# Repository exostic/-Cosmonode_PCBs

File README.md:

# Cosmonode v0.7

Universal node, plug and play extensions to ease sensors connection.

## Features

	- Compile and flash with Arduino IDE
	- MCU = ATMega328P-AU
	- radio = RN2483 / RFM69CW ( communications based on LoRaWan or MySensors protocol )
	- 3.3V regulation ( XC6206P332MR )
	- Powered by 3.7V LiPo battery ( 2 pins JST connector )
	- Battery charging ( MCP7831 )
	- State LED's
	- Jumpers to activate radio reset, LED's, on/off switch
	- Button for reset / config mode, or anything else!
	- ATSHA204 to allow hardware unique signature ( no use with RN2483 )

## Projects

Each directory contains Kicad plans, 3D plans, gerber, descriptive .png and .pdf files.

	- ext01 : BME280, Temperature + Humidity + Pression sensor ( only here for the footprint )
	- ext02 : XKC-Y25, Liquid level sensor
	- ext03 : Various connectors ( I2C, Digital, Analog )
	- ext04 : PT100 3 wire, Temperature sensor
	- ext05 : ISP header + micro USB to TTL 
	- ext06 : Analog pH Sensor - BNC probe (WIP)
	- ext07 : MHZ19, CO2 sensor

## Board pinout

	A0 = /
	A1 = /
	A2 = ATSHA204 Input
	A3 = Battery voltage report
	A4 = SDA
	A5 = SCL
	A6 = * LED, jumper J9 ( used as RN2483 Tx )
	A7 = * LED, jumper J14 ( used as RN2483 Rx )
	D0 = RX
	D1 = TX
	D2 = * WakeInterrupt from RN2483, jumper J6 - RFM69 DI0
	D3 = ButtonInterrupt, jumper JP2 ( used to chose mode )
	D4 = /
	D5 = /
	D6 = /
	D7 = /
	D8 = /
	D9 = * RN2483 Reset, jumper J3 - RFM69 Reset
	D10 = RN2483 Rx - RFM69 NSS
	D11 = RN2483 Tx - RFM69 MOSI
	D12 = RFM69 MISO
	D13 = RFM69 SCK
	*optionnal, solder jumper

## Roadmap

--> changelog.md

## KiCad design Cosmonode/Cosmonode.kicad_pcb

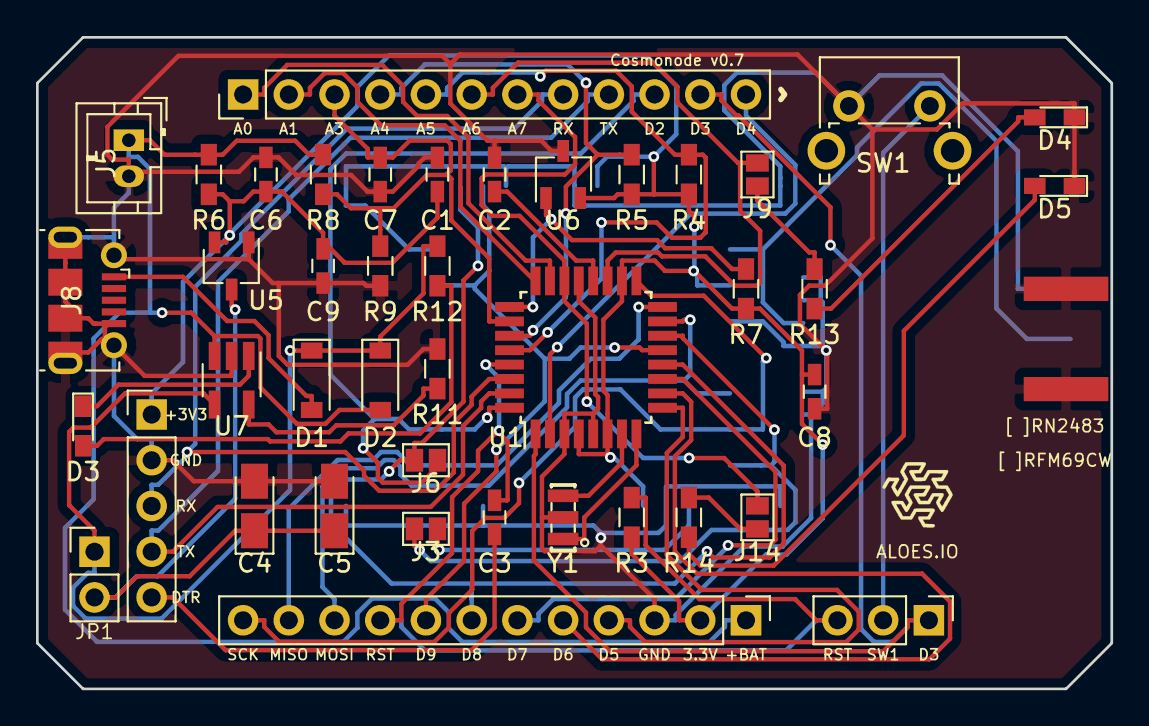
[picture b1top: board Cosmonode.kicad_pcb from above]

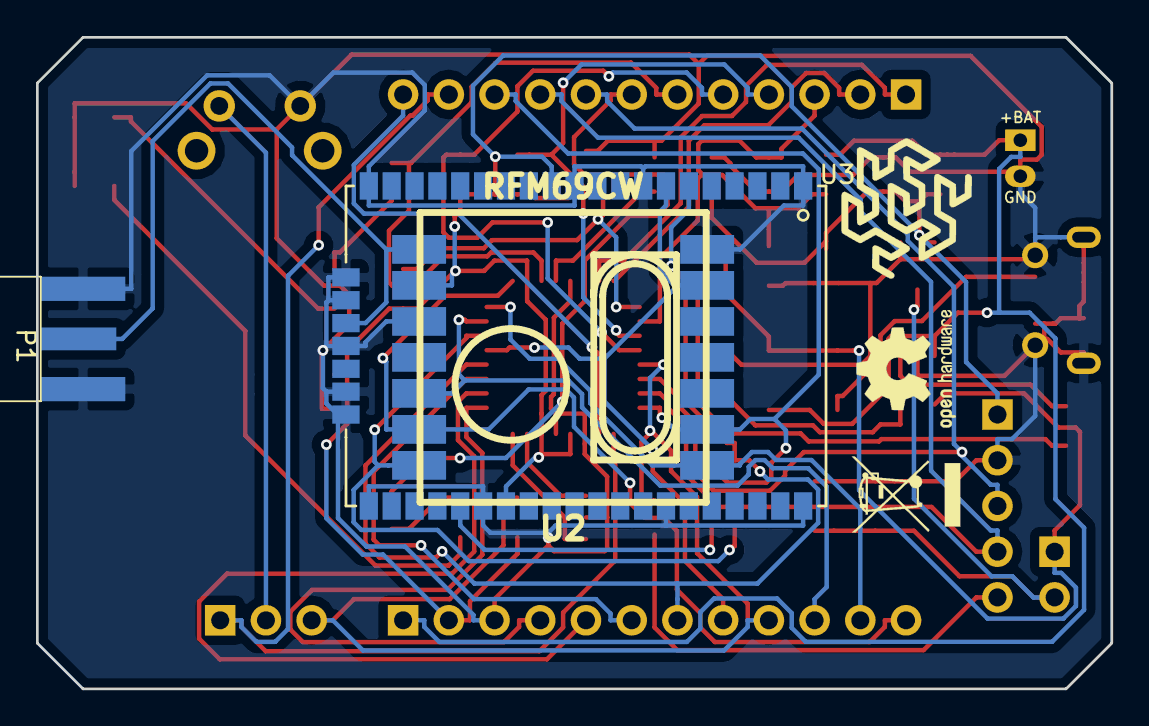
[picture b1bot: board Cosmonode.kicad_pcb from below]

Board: 2 copper layers, 59.7 x 36.2 mm, 49 parts (6 on the bottom side), 43 nets.

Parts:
C1, C2, C3, C7, C8, C9: 100nF; C_0603_HandSoldering
C4, C5: 47uF; CP_Tantalum_Case-A_EIA-3216-18_Reflow
C6: 4.7uF; C_0603_HandSoldering
D1, D2: MBR0520; D_SOD-123
D3, D4, D5: LED; LED_0603_HandSoldering
J1, J2: CONN_01X12; Pin_Header_Straight_1x12_Pitch2.54mm
J3, J6, J9, J14: GS2
J4: OSHW; OSHW-Logo2_7.3x6mm_SilkScreen
J5: CONN_01X02; JST_PH_B2B-PH-K_02x2.00mm_Straight
J8: USB_OTG; USB_Micro-B_Molex-105017-0001
J10: WEEE_Logo; WEEE-Logo_4.2x6mm_SilkScreen
J11: Aloes_Logo; Aloes
J12: Aloes_mini_Logo; Aloes_mini
J13: CONN_01X05; Pin_Header_Straight_1x05_Pitch2.54mm
JP1: Jumper_NO_Small; Pin_Header_Straight_1x02_Pitch2.54mm
JP2: Jumper_NC_Dual; Pin_Header_Straight_1x03_Pitch2.54mm
P1: COAX; EDGE_SMA_5
R3: 10k; R_0603_HandSoldering
R4, R5, R12, R13, R14: 1k; R_0603_HandSoldering
R6: 0; R_0603_HandSoldering
R7: 100k; R_0603_HandSoldering
R8: 1M; R_0603_HandSoldering
R9: 470k; R_0603_HandSoldering
R11: R; R_0603_HandSoldering
SW1: SW_DIP_x01; SW_Tactile_SPST_Angled_PTS645Vx58-2LFS
U1: ATMEGA328P-AU; TQFP-32_7x7mm_Pitch0.8mm
U2: RFM69CW; RFM12B_SMD
U3: RN2483
U5: XC6206P332MR; TSOT-23
U6: ATSHA204; TSOT-23
U7: MCP73811T-420I/OT; SOT-23-5_HandSoldering
Y1: Crystal_GND2; X3-SMD-3.6X1.3X0.8MM

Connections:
+3V3: C1.1, C6.1, C8.2, C9.1, J2.2, J13.1, R3.1, R4.1, R5.1, R6.1, R7.2, U1.4, U1.6, U1.18, U2.9, U3.12, U3.34, U5.2, U6.2
+BATT: D2.2, J2.1, J5.1, R6.2, R8.1, U7.3
/AREF: C2.2, U1.20
/RN2483_RST: J3.1, U3.32
A0: J1.1, U1.23
A1: J1.2, U1.24
A2: R7.1, U1.25, U6.1
A3: C7.2, J1.3, R8.2, R9.1, U1.26
A4: J1.4, R5.2, U1.27
A5: J1.5, R4.2, U1.28
A6: J1.6, J9.2, U1.19
A7: J1.7, J14.2, U1.22
ANT: P1.1, U2.8, U3.23
D2: J1.10, J6.1, U1.32, U2.2
D3: J1.11, JP2.1, U1.1
D4: J1.12, U1.2
D5: J2.4, U1.9
D6: J2.5, U1.10
D7: J2.6, U1.11
D8: J2.7, J6.2, U1.12, U3.6
D9: J2.8, U1.13, U2.6, U3.7
D10: J3.2, U1.14, U2.14
D11/MOSI: J2.10, U1.15, U2.12
D12/MISO: J2.11, U1.16, U2.1
D13/SCK: J2.12, U1.17, U2.13
DTR: C3.2, J13.5
GND: C1.2, C2.1, C4.2, C5.2, C6.2, C7.1, C8.1, C9.2, D4.1, D5.1, J2.3, J5.2, J8.5, J8.6, J13.2, P1.2, P1.3, P1.4, P1.5, R9.2, R11.1, SW1.1, U1.3, U1.5, U1.21, U2.7, U2.10, U3.1, U3.8, U3.11, U3.20, U3.21, U3.22, U3.24, U3.26, U3.27, U3.28, U3.33, U3.41, U3.47, U5.1, U6.3, U7.2, Y1.2
unnamed: C4.1, C5.1, JP1.2, U5.3
unnamed: D1.1, D2.1, JP1.1, R12.2, U7.4
unnamed: D3.1, U7.1
unnamed: D3.2, R12.1
unnamed: D4.2, R13.1
unnamed: D5.2, R14.1
unnamed: J9.1, R13.2
unnamed: J14.1, R14.2
unnamed: JP2.2, SW1.2
unnamed: R11.2, U7.5
unnamed: U1.7, Y1.3
unnamed: U1.8, Y1.1
RST: C3.1, J2.9, JP2.3, R3.2, U1.29
RX: J1.8, J13.3, U1.30
TX: J1.9, J13.4, U1.31
VDD: D1.2, J8.1

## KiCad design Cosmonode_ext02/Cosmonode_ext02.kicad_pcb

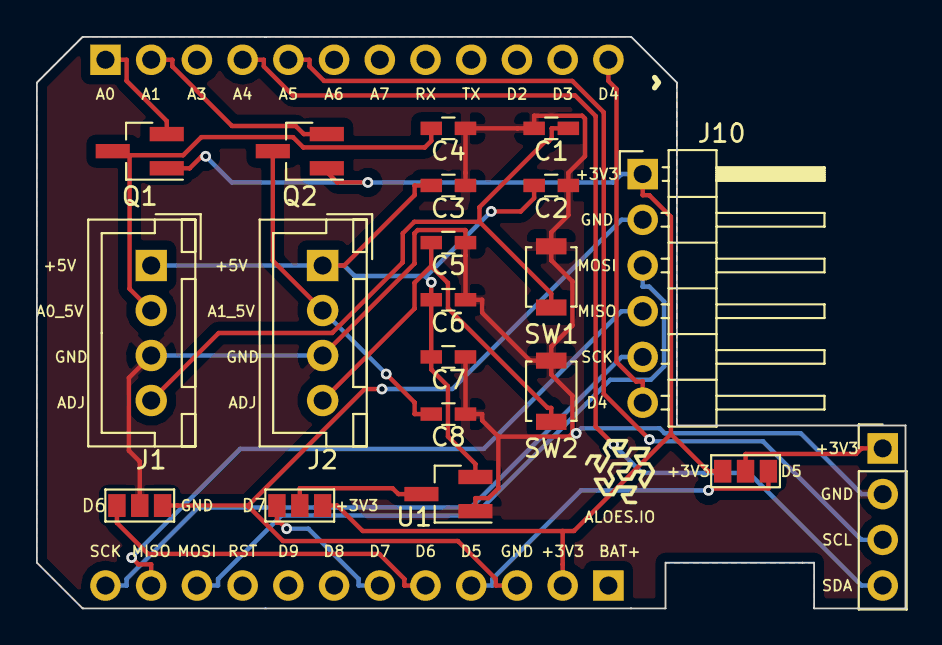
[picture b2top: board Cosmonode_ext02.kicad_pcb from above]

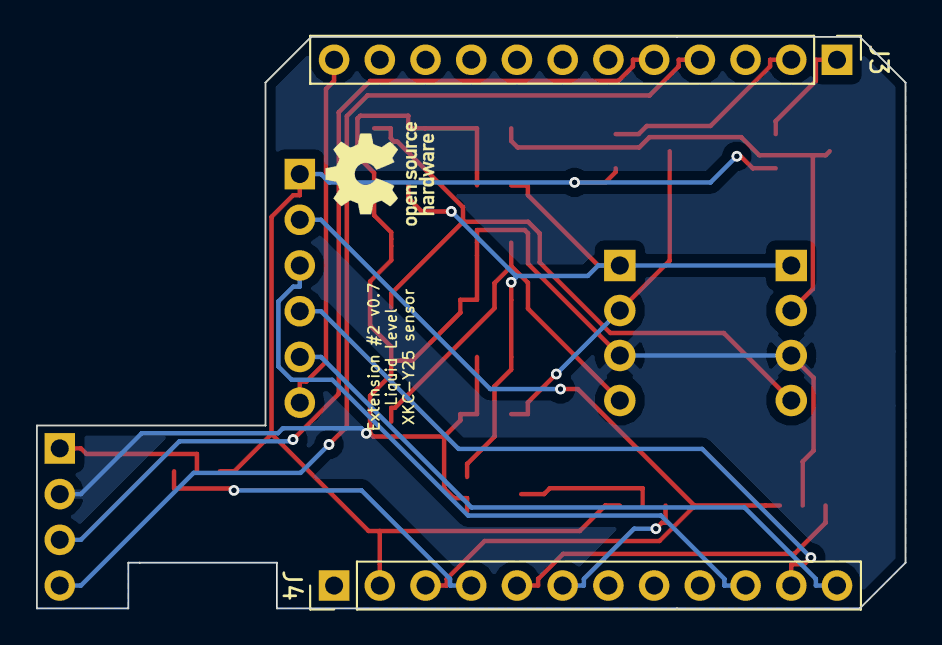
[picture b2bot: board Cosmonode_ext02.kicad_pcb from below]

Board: 2 copper layers, 48.3 x 31.8 mm, 24 parts (3 on the bottom side), 21 nets.

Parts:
C1, C3, C4, C5, C7, C8: 100nF; C_0603_HandSoldering
C2, C6: 10uF; C_0603_HandSoldering
J1, J2: CONN_01X04; JST_XH_B04B-XH-A_04x2.50mm_Straight
J3, J4: CONN_01X12; Socket_Strip_Straight_1x12_Pitch2.54mm
J5, J6, J12: GS3
J7: Aloes_Logo; Aloes_mini
J8: OSHW_Logo; OSHW-Logo_5.7x6mm_SilkScreen
J9: CONN_01X04; Socket_Strip_Straight_1x04_Pitch2.54mm
J10: CONN_01X06; Pin_Header_Angled_1x06_Pitch2.54mm
Q1, Q2: BSS138; SOT-23_Handsoldering
SW1, SW2: SW_Push; SW_SPST_B3U-1000P
U1: XC6206P502MR; SOT-23_Handsoldering

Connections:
+3V3: J4.2, J5.3, J10.1, J12.3, Q1.1, Q2.1
+5V: C2.1, C3.1, C6.1, C7.1, J1.1, J2.1, U1.2
A0: J3.1, Q1.2
A0_5V: C4.1, J1.2, Q1.3
A1: J3.2, Q2.2
A1_5V: C8.1, J2.2, Q2.3
A4: J3.4, J9.4
A5: J3.5, J9.3
D4: J3.12, J10.6
D5: J4.4, J12.1
D6: J4.5, J6.1
D7: J4.6, J5.1
GND: J4.3, J6.3, J10.2
MISO: J4.11, J10.4
MOSI: J4.10, J10.3
unnamed: C1.1, C2.2, C3.2, C4.2, C5.1, C6.2, C7.2, C8.2, J1.3, J2.3, J6.2, J9.2, SW1.2, SW2.2, U1.1
unnamed: C1.2, J1.4, SW1.1
unnamed: C5.2, J2.4, SW2.1
unnamed: J5.2, U1.3
unnamed: J9.1, J12.2
SCK: J4.12, J10.5

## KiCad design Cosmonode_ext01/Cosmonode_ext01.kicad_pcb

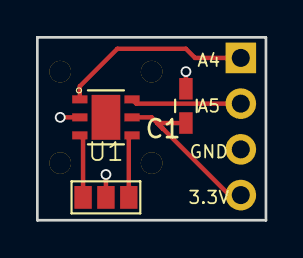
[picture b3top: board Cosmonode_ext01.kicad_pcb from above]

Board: 2 copper layers, 12.7 x 10.2 mm, 8 parts (1 on the bottom side), 6 nets.

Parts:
C1: 100nF; C_0603_HandSoldering
J1: CONN_01X04; Pin_Header_Angled_1x04_Pitch2.54mm
J2, J4, J5, J6: CONN_01X01; SolderWirePad_single_1-2mmDrill
J3: GS3
U1: SI7020-A20-YM0R; SON100P300X300X80-7N

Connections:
+3V3: C1.1, J1.4, U1.5
A4: J1.1, U1.1
A5: J1.2, U1.6
GND: C1.2, J1.3, J3.2, U1.2
unnamed: J3.1, U1.4
unnamed: J3.3, U1.3

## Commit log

2018-01-22 start v0.8
